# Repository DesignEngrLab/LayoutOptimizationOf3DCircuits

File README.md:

# LayoutOptimizationOf3DCircuits
A thermal-aware optimization for component placement and routing for electronic parts in 3D spacce in order to design and create 3D circuits/PCBs. The main objective of the entire process is to minimize total routing length which corresponds to minimum resistance and signal delay.

The optimization process consists of two main stages. 

The first stage is component placement in which a simulated annealing algorithm is used to place the electrical components in a pre-defined 3D container. The optimization process uses direct line distance between component pins.

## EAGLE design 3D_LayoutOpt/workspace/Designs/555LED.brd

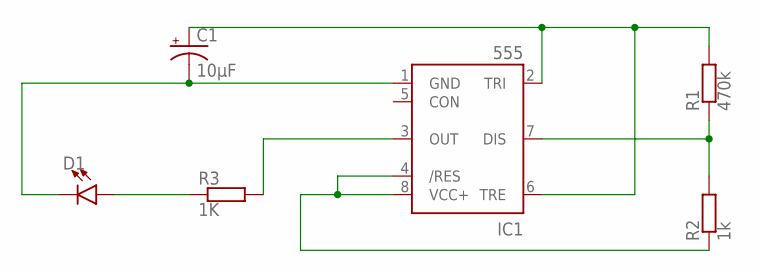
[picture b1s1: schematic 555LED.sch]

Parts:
C1: 10µF; EIA6032-NOM
D1: LED1206; LED-1206
IC1: 555; SO08
R1: 470k; BVS
R2: 1k; BVS
R3: 1K; BVS

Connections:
unnamed: IC1.3 (OUT), R3.1
unnamed: D1.A, R3.2
unnamed: IC1.4 (/RES), IC1.8 (VCC+), R2.2
unnamed: C1.C (-), D1.C, IC1.1 (GND)
unnamed: C1.A (+), IC1.2 (TRI), IC1.6 (TRE), R1.1
unnamed: IC1.7 (DIS), R1.2, R2.1

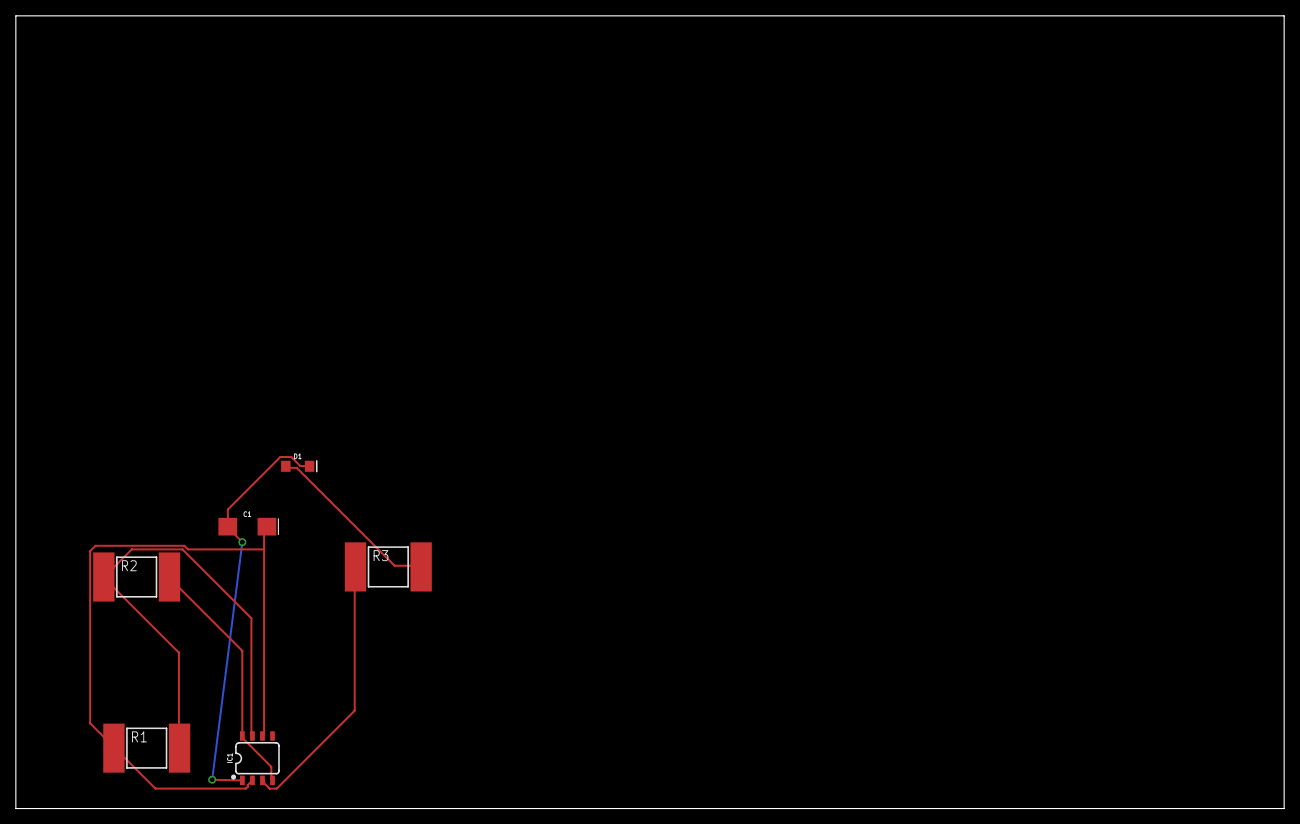
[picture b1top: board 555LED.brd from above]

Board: 2 copper layers, 160.0 x 100.0 mm, 6 parts (0 on the bottom side), 6 nets.

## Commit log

2016-10-05 initial push of old C code from 1995
2016-12-13 made a new project during meeting
2017-02-08 Converted almost everything from C to C#.
2017-02-23 Fixed more errors.
2017-02-23 fixed more errors!
2017-02-23 more fixes!
2017-02-25 The solution can be built successfully - need to fix index range errors
2017-02-26 Changed the while loops to for loops, orgonized code.
2017-02-26 Changed char arrays to strings.
2017-02-26 Changed more while-loops to for-loops.
2017-02-26 Cleaned up more code.
2017-03-01 More cleaning up.
2017-03-02 made a workspace directory and need to put files there
2017-03-09 Resolved issues with null refrences and index range. Resolved problem with writing to files.
2017-03-23 made changes for tessellated version of the algorithm
2017-03-23 ImportFootprints works now, problem with loading components without specified packages.
2017-03-25 Implemented variables and functions needed for importing the "Netlist".
2017-04-06 Implemented the new overlap functions and the initialize location function.
2017-04-12 implemented new translate methods for tessellated solids.
2017-04-12 Implemented the methods for transforming the solids and the PIN coordinates.
2017-04-12 Updeted the "swap" method to be compatible with tessellated solids.
2017-04-12 Added backup variables to the Component class in order to store the state before taking a step, added a method to "swap" method to update PIN coordinates.
2017-04-12 Added the component backup method to the "Component" class.
2017-04-12 Updating design variable is done using a for-loop now.
2017-04-12 All the backup methods are grouped inside another method called "Backup".
2017-04-13 Updated the "Revert" method.
2017-04-13 Added a new method to check if center of any component is outside of container's AABB. If so reject the step.
2017-04-13 Updated more methods, cleaned up some code.
2017-04-13 Corrected number of objectives in the main objective function, more clean up.
2017-04-13 Using OOOT for optimization.
2017-04-13 Added Netlist total length to the objective function, added a method inside the "Net" class to calculate the Netlength.
2017-04-14 Can build the solution now.
2017-04-17 lots of changes to put in OOOT format
2017-04-17 borrowed from Move and Swap to establish new component.Update function. this needs to be carefully checked during debug
2017-04-19 Added component and container CAD models, sch and brd files to the Design folder.
2017-04-20 The container and the components are loaded in correctly, TVGL and MIConvexhull are added as projects.
2017-04-26 Corrected datafile1 and datafile2
2017-04-26 Corrected the Update method in Component class. The update method now calls another method to set the component to zero and then transorms it.
2017-04-26 Solved the issue with creating coordinate arrays with 4 elements when using "SetCompToZero" method.
2017-04-26 Corrected the "Update" method again, corrected minor issues with design variables.
2017-04-26 Resolved minor issues with indexing.
2017-04-27 Resolved the issue with importing pins, each SMD now has a pin name associated with it.
2017-05-01 made a lot of changes, the code runs for now but no results yet. Need to implent a new method for calculating net lengths.
2017-05-02 Added Presenter but the code is not working now.
2017-05-02 Resolved the issue with presenter, still has errors about threads.
2017-05-03 The code runs now!
2017-05-03 adding ooot to get into more detail
2017-05-18 Added some code for the routing process.
2017-05-18 Component-Component overlap claculater now first checks the bounding boxes then convex hulls and finally the overlapping volume.
2017-05-18 Component-Container overlap claculater now first checks the bounding boxes then convex hulls and finally the overlapping volume. Deleted unnecessary files.
2017-05-22 RatsNest is implemented. "Net" coordinates are not calculated correctly.
2017-05-25 Solved the issue with routing,
2017-05-25 Solved the problem with the tranformation matrix and Netlist evaluaton.
2017-05-27 Removed unnecessary code.
2017-05-28 Removed the bug with indexing, implemented a new way to calculate collision penalty. getting better results now!
2017-06-02 Resolved the bug with component initial locations.
2017-09-07 Code works!

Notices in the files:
parts and their libraries:
SparkFun-Capacitors: Licensing: Creative Commons ShareAlike 4.0 International - https://creativecommons.org/licenses/by-sa/4.0
